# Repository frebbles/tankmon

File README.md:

# TankMon

A no frills dual tank water level monitoring solution incorporating:

- ESP8266 low power ultrasonic measurer remote monitor and reporter device for dual tank setups [tankmon-probedual] 
Open this in Arduino, ensure that ESP8266 is installed as per the [Adafruit esp8266 arduino guide](https://learn.adafruit.com/adafruit-io-basics-esp8266-arduino/using-arduino-ide)

- PHP server receiver and graph display tool [tankmon]

- OpenSCAD construction for Ultrasonic case and ESP8266/NODEMCU case [tankmon-cases]

- Circuit Design and construction for remote monitor circuit and board pcb in KiCAD [tankmon-pcb]

A demonstration exercise in, simplifying workflows and modularity, utilising Arduino, NodeMCU, KiCAD, OpenSCAD.

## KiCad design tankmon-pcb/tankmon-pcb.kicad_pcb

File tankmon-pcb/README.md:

TANKMON NodeMCU PCB adaptor for ultrasonic sensors

These have been designed using KiCAD 5.1.2

Open the project in KiCAD to view/modify the PCB. Export to gerber for sending to your friendly board house for production.

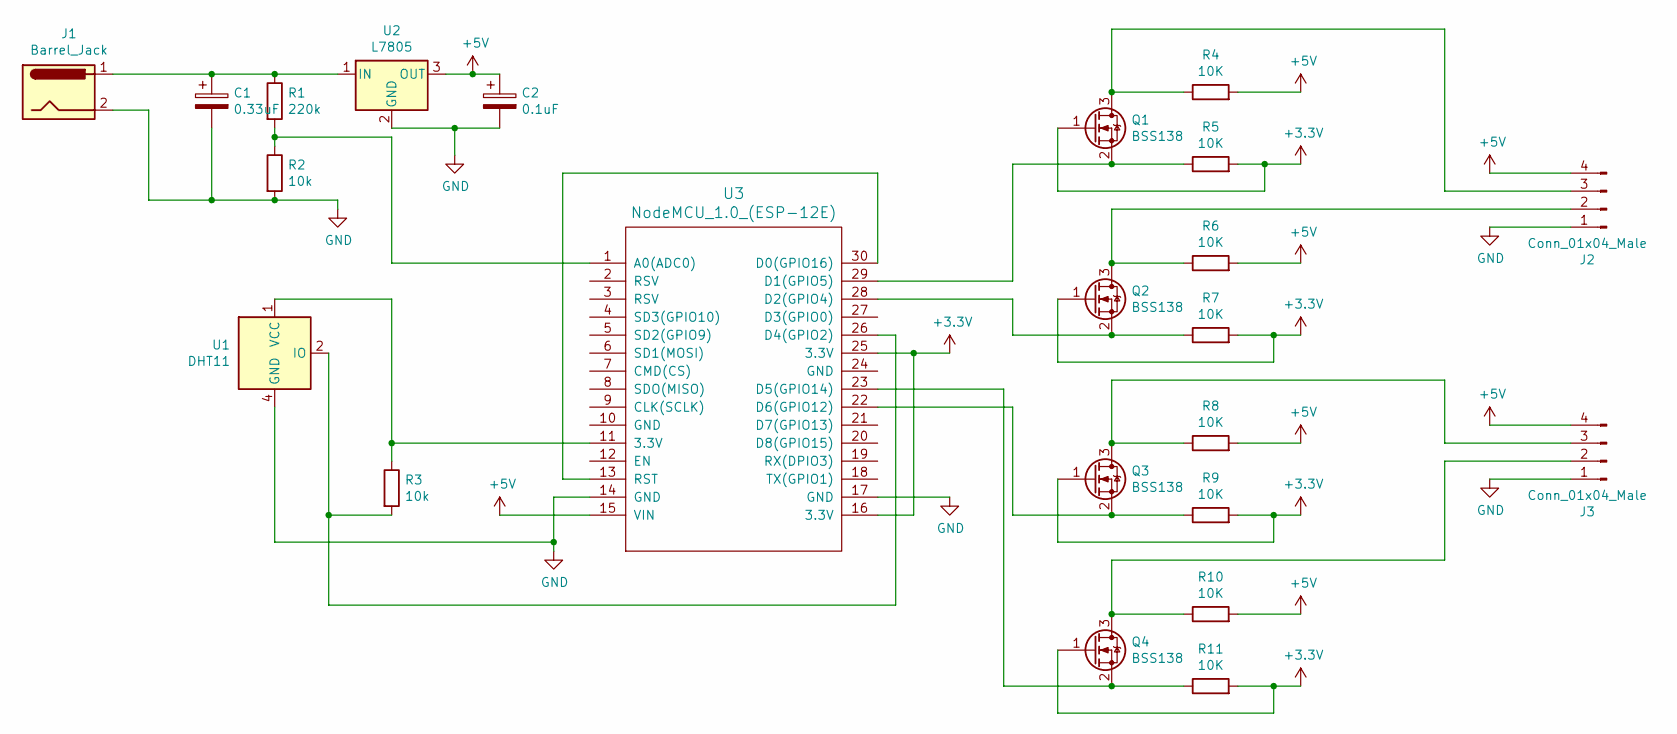
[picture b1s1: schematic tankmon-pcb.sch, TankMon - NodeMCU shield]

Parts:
C1: 0.33uF; C_Radial_D5.0mm_H5.0mm_P2.00mm
C2: 0.1uF; C_Radial_D5.0mm_H5.0mm_P2.00mm
J1: Barrel_Jack; BarrelJack_Horizontal
J2, J3: Conn_01x04_Male; PinHeader_1x04_P2.54mm_Vertical
Q1, Q2, Q3, Q4: BSS138; SOT-23
R1: 220k; R_0603_1608Metric
R2, R3: 10k; R_0603_1608Metric
R4, R5, R6, R7, R8, R9, R10, R11: 10K; R_0603_1608Metric
U1: DHT11; Aosong_DHT11_5.5x12.0_P2.54mm
U2: L7805; TO-220-3_Horizontal_TabDown
U3: NodeMCU_1.0_(ESP-12E); ESP12F-Devkit-V3

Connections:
+3V3: Q1.1 (G), Q2.1 (G), Q3.1 (G), Q4.1 (G), R5.2, R7.2, R9.2, R11.2, U3.16 (3.3V), U3.25 (3.3V)
+5V: C2.1, J2.4, J3.4, R4.2, R6.2, R8.2, R10.2, U2.3 (OUT), U3.15 (VIN)
GND: C1.2, C2.2, J1.2, J2.1, J3.1, R2.2, U1.4 (GND), U2.2 (GND), U3.14 (GND), U3.17 (GND)
unnamed: C1.1, J1.1, R1.1, U2.1 (IN)
unnamed: J2.2, Q2.3 (D), R6.1
unnamed: J2.3, Q1.3 (D), R4.1
unnamed: J3.2, Q4.3 (D), R10.1
unnamed: J3.3, Q3.3 (D), R8.1
unnamed: Q1.2 (S), R5.1, U3.29 (D1(GPIO5))
unnamed: Q2.2 (S), R7.1, U3.28 (D2(GPIO4))
unnamed: Q3.2 (S), R9.1, U3.22 (D6(GPIO12))
unnamed: Q4.2 (S), R11.1, U3.23 (D5(GPIO14))
unnamed: R1.2, R2.1, U3.1 (A0(ADC0))
unnamed: R3.1, U1.1 (VCC), U3.11 (3.3V)
unnamed: R3.2, U1.2 (IO), U3.26 (D4(GPIO2))
unnamed: U3.13 (RST), U3.30 (D0(GPIO16))

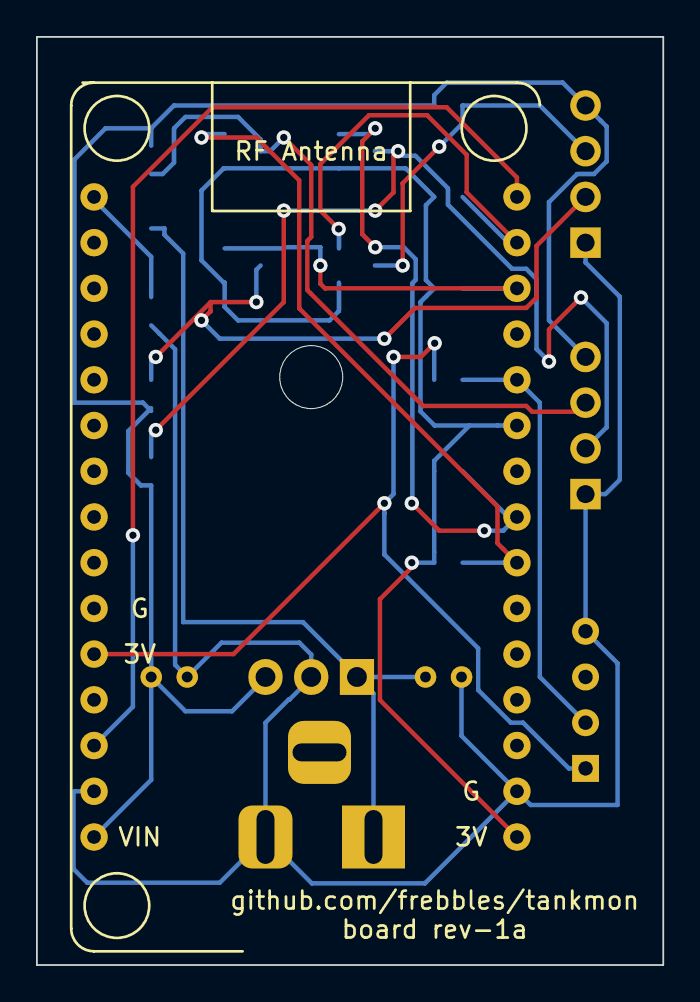
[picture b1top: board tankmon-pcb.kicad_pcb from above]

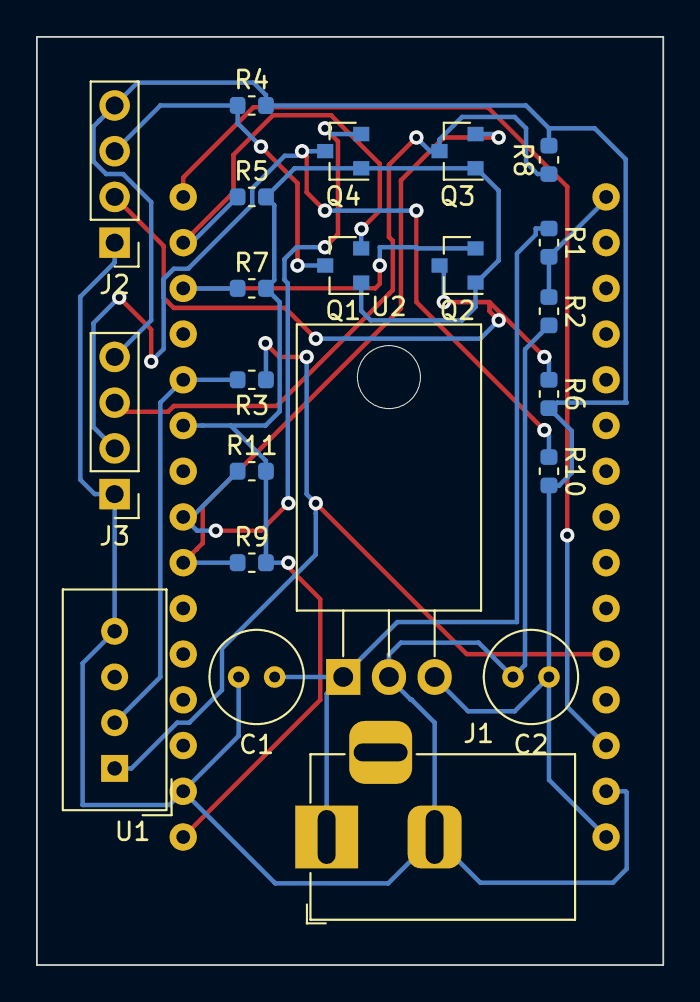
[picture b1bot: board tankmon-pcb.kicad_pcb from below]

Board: 2 copper layers, 34.8 x 51.6 mm, 23 parts (22 on the bottom side), 16 nets.

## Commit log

2019-09-21 Tweak avoiding neg tank volume values
2019-12-27 Changed graphing display to be one week of history
2020-05-07 Readme updated
